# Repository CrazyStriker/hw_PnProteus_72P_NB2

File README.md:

# hw_PnProteus_72P_NB2
PnP adapter board for 72P miata NB2 ECU using Proteus Rusefi compatible board

Onboard debug leds for injectors and ignition as well as vital functions
Clear and simple silk
Fits in the stock ECU case
2x 23 pins ampseal connectors for extended functionalities provided by proteus

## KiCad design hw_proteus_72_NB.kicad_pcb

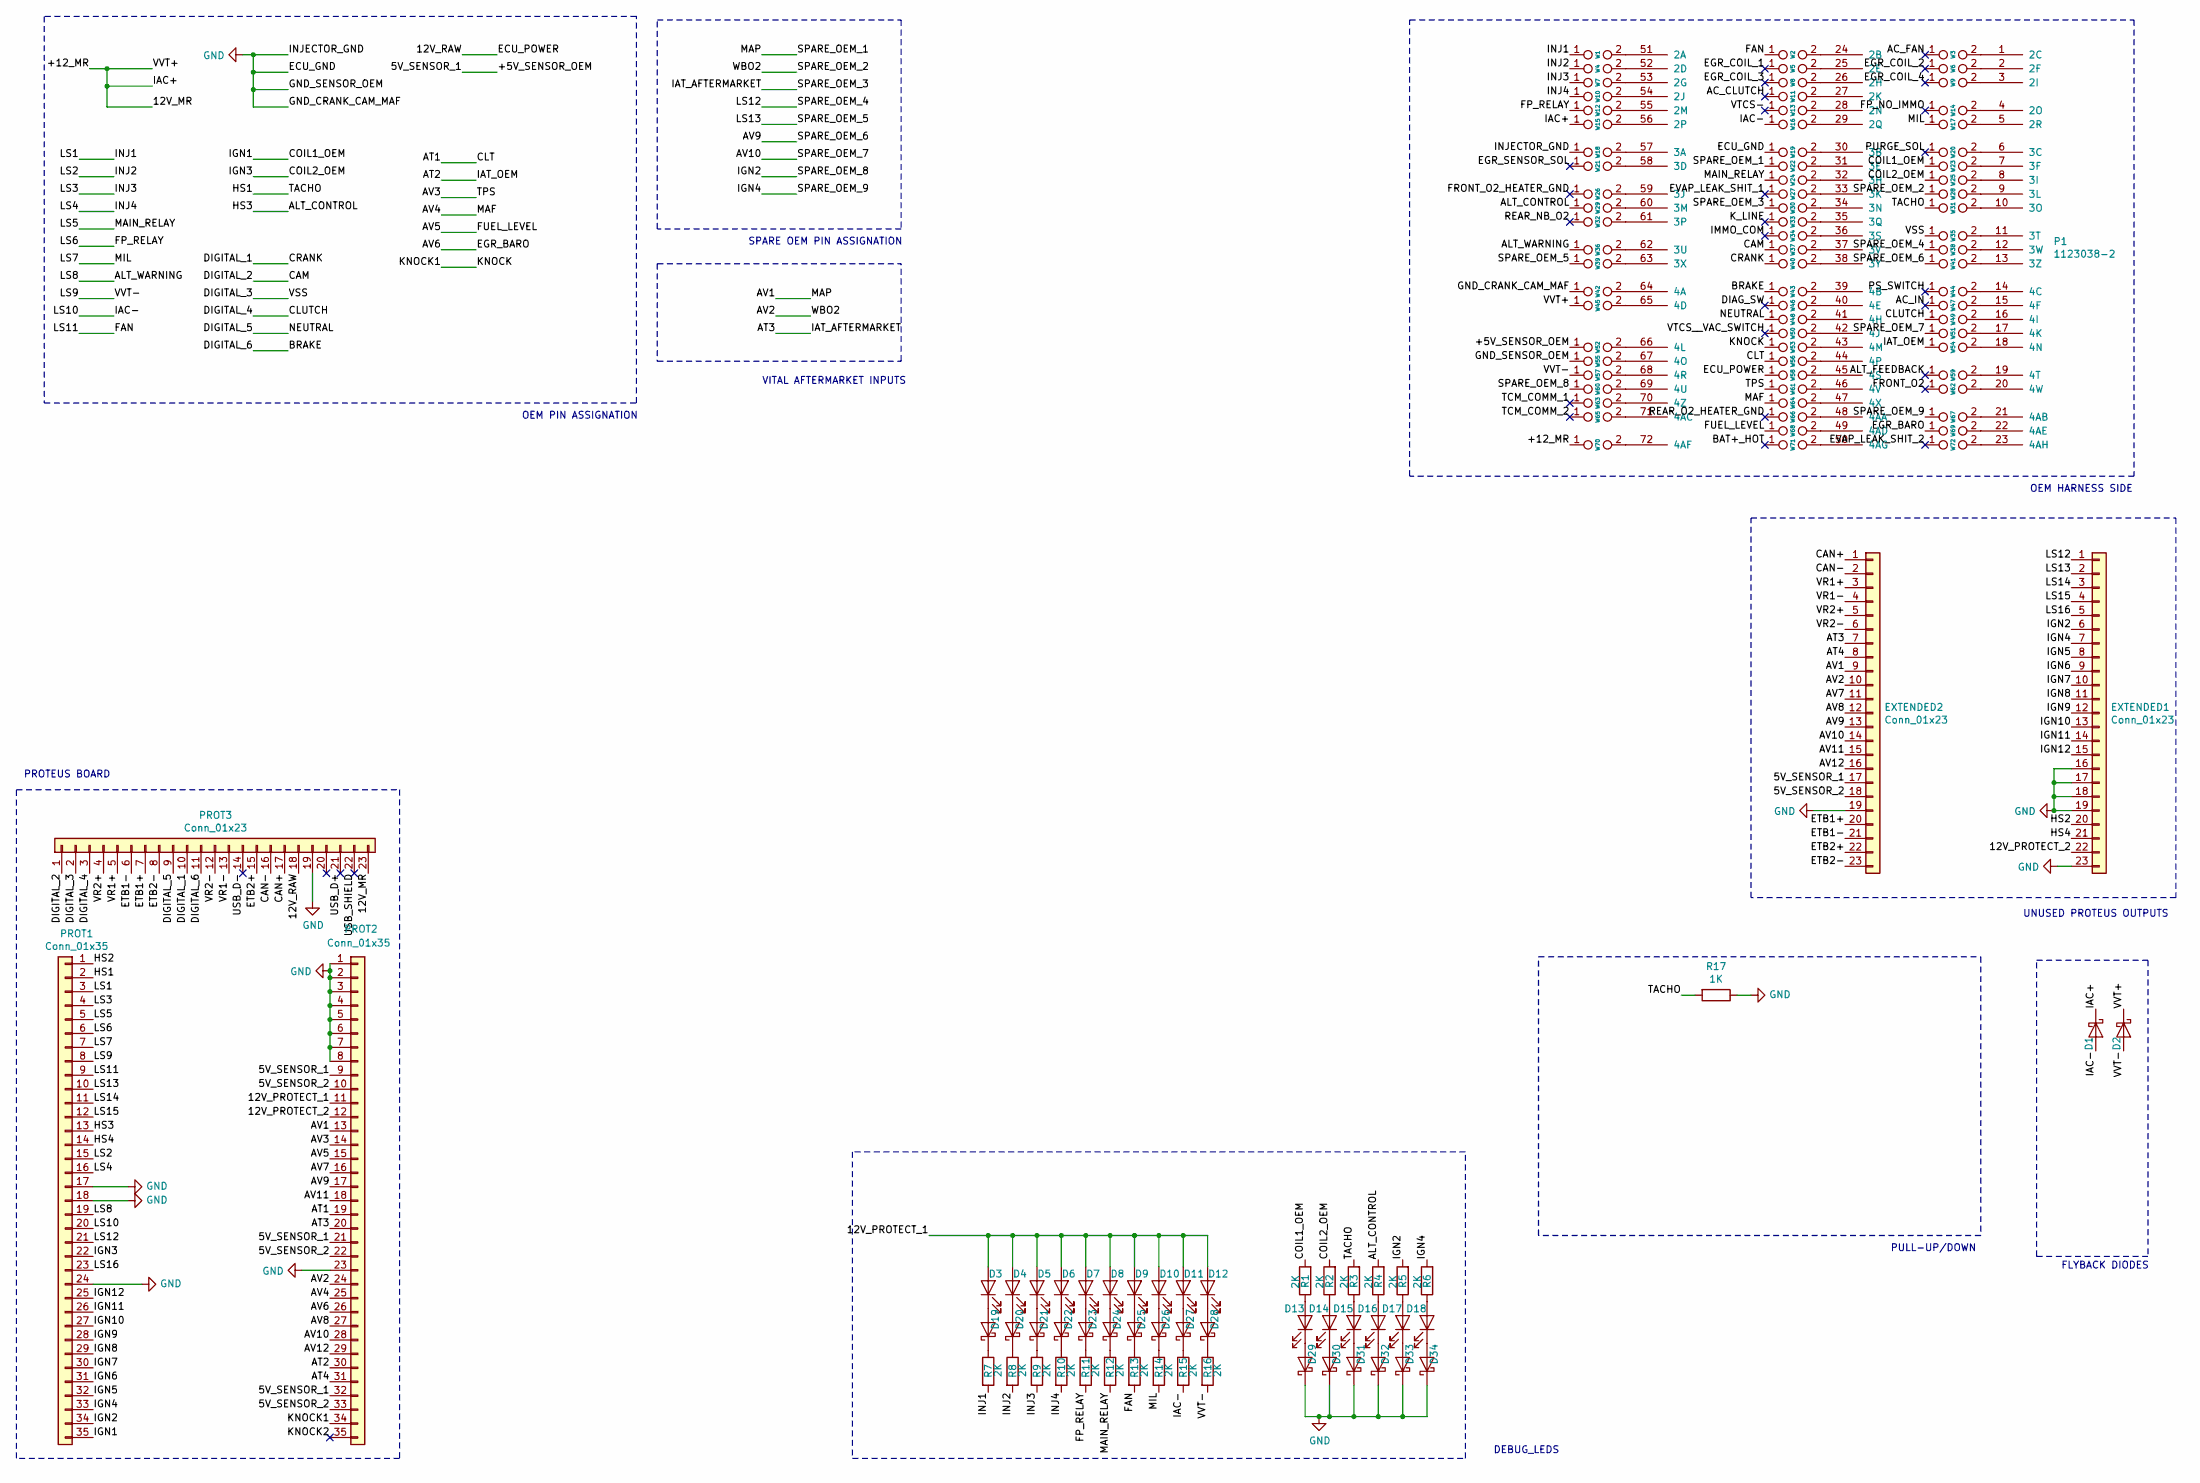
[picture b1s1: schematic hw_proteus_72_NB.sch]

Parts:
D1, D2, D19, D20, D21, D22, D23, D24, D25, D26, D27, D28, D29, D30, D31, D32, D33, D34: D_Schottky; D_SOD-123F
D3, D4, D5, D6, D7, D8, D9, D10, D11, D12, D13, D14, D15, D16, D17, D18: LED; LED_0603_1608Metric_Castellated
EXTENDED1, EXTENDED2: Conn_01x23; ampseal-23
P1: 1123038-2
PROT1, PROT2: Conn_01x35; ampseal-35
PROT3: Conn_01x23; ampseal-23
R1, R2, R3, R4, R5, R6, R7, R8, R9, R10, R11, R12, R13, R14, R15, R16: 2K; R_0603_1608Metric
R17: 1K; R_0201_0603Metric
W1, W2, W3, W4, W5, W6, W7, W8, W9, W10, W11, W12, W13, W14, W15, W16, W17, W18, W19, W20, W21, W22, W23, W24, W25, W26, W27, W28, W29, W30, W31, W32, W33, W34, W35, W36, W37, W38, W39, W40, W41, W42, W43, W44, W45, W46, W47, W48, W49, W50, W51, W52, W53, W54, W55, W56, W57, W58, W59, W60, W61, W62, W63, W64, W65, W66, W67, W68, W69, W70, W71, W72: TestPoint_2Pole; SM0805_jumper

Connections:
/5V_SENSOR_2: EXTENDED2.18, PROT2.10, PROT2.22, PROT2.33
/12V_PROTECT_1: D3.2 (A), D4.2 (A), D5.2 (A), D6.2 (A), D7.2 (A), D8.2 (A), D9.2 (A), D10.2 (A), D11.2 (A), D12.2 (A), PROT2.11
/12V_PROTECT_2: EXTENDED1.22, PROT2.12
/12V_RAW: PROT3.18, W58.1
/+5V_SENSOR_OEM: EXTENDED2.17, PROT2.9, PROT2.21, PROT2.32, W52.1
/+12_MR: D1.1 (K), D2.1 (K), PROT3.23, W15.1, W45.1, W70.1
/AC_CLUTCH: W11.1
/AC_FAN: W3.1
/AC_IN: W47.1
/ALT_CONTROL: PROT1.13, R4.2, W29.1
/ALT_FEEDBACK: W59.1
/ALT_WARNING: PROT1.19, W36.1
/AT1: PROT2.19, W56.1
/AT2: PROT2.30, W54.1
/AT3: EXTENDED2.7, PROT2.20, W30.1
/AT4: EXTENDED2.8, PROT2.31
/AV1: EXTENDED2.9, PROT2.13, W22.1
/AV2: EXTENDED2.10, PROT2.24, W28.1
/AV3: PROT2.14, W61.1
/AV4: PROT2.25, W64.1
/AV5: PROT2.15, W68.1
/AV6: PROT2.26, W69.1
/AV7: EXTENDED2.11, PROT2.16
/AV8: EXTENDED2.12, PROT2.27
/AV9: EXTENDED2.13, PROT2.17, W41.1
/AV10: EXTENDED2.14, PROT2.28, W51.1
/AV11: EXTENDED2.15, PROT2.18
/AV12: EXTENDED2.16, PROT2.29
/BAT+_HOT: W71.1
/BRAKE: PROT3.11, W43.1
/CAM: PROT3.1, W37.1
/CAN+: EXTENDED2.1, PROT3.17
/CAN-: EXTENDED2.2, PROT3.16
/CLUTCH: PROT3.3, W49.1
/COIL1_OEM: PROT1.35, R1.2, W23.1
/COIL2_OEM: PROT1.22, R2.2, W25.1
/CRANK: PROT3.10, W40.1
/DIAG_SW: W46.1
/DIGITAL_3: PROT3.2, W35.1
/DIGITAL_5: PROT3.9, W48.1
/EGR_COIL_1: W5.1
/EGR_COIL_2: W6.1
/EGR_COIL_3: W8.1
/EGR_COIL_4: W9.1
/EGR_SENSOR_SOL: W21.1
/ETB1+: EXTENDED2.20, PROT3.7
/ETB1-: EXTENDED2.21, PROT3.6
/ETB2+: EXTENDED2.22, PROT3.15
/ETB2-: EXTENDED2.23, PROT3.8
/EVAP_LEAK_SHIT_1: W27.1
/EVAP_LEAK_SHIT_2: W72.1
/FAN: PROT1.9, R13.2, W2.1
/FP_NO_IMMO: W14.1
/FP_RELAY: PROT1.6, R11.2, W12.1
/FRONT_O2: W62.1
/FRONT_O2_HEATER_GND: W26.1
/HS1: PROT1.2, R3.2, R17.2, W31.1
/HS2: EXTENDED1.20, PROT1.1
/HS4: EXTENDED1.21, PROT1.14
/IAC-: D1.2 (A), PROT1.20, R15.2, W16.1
/IGN2: EXTENDED1.6, PROT1.34, R5.2, W60.1
/IGN4: EXTENDED1.7, PROT1.33, R6.2, W67.1
/IGN5: EXTENDED1.8, PROT1.32
/IGN6: EXTENDED1.9, PROT1.31
/IGN7: EXTENDED1.10, PROT1.30
/IGN8: EXTENDED1.11, PROT1.29
/IGN9: EXTENDED1.12, PROT1.28
/IGN10: EXTENDED1.13, PROT1.27
/IGN11: EXTENDED1.14, PROT1.26
/IGN12: EXTENDED1.15, PROT1.25
/IMMO_COM: W34.1
/INJ1: PROT1.3, R7.2, W1.1
/INJ2: PROT1.15, R8.2, W4.1
/INJ3: PROT1.4, R9.2, W7.1
/INJ4: PROT1.16, R10.2, W10.1
/KNOCK: PROT2.34, W53.1
/KNOCK2: PROT2.35
/K_LINE: W33.1
/LS5: PROT1.5, R12.2, W24.1
/LS7: PROT1.7, R14.2, W17.1
/LS9: D2.2 (A), PROT1.8, R16.2, W57.1
/LS12: EXTENDED1.1, PROT1.21, W38.1
/LS13: EXTENDED1.2, PROT1.10, W39.1
/LS14: EXTENDED1.3, PROT1.11
/LS15: EXTENDED1.4, PROT1.12
/LS16: EXTENDED1.5, PROT1.23
/PS_SWITCH: W44.1
/PURGE_SOL: W20.1
/REAR_NB_O2: W32.1
/REAR_O2_HEATER_GND: W66.1
/TCM_COMM_1: W63.1
/TCM_COMM_2: W65.1
/USB_D+: PROT3.21
/USB_D-: PROT3.14
/USB_SHIELD: PROT3.22
/VR1+: EXTENDED2.3, PROT3.5
/VR1-: EXTENDED2.4, PROT3.13
/VR2+: EXTENDED2.5, PROT3.4
/VR2-: EXTENDED2.6, PROT3.12
/VTCS-: W13.1
/VTCS__VAC_SWITCH: W50.1
GND: D29.1 (K), D30.1 (K), D31.1 (K), D32.1 (K), D33.1 (K), D34.1 (K), EXTENDED1.16, EXTENDED1.17, EXTENDED1.18, EXTENDED1.19, EXTENDED1.23, EXTENDED2.19, PROT1.17, PROT1.18, PROT1.24, PROT2.1, PROT2.2, PROT2.3, PROT2.4, PROT2.5, PROT2.6, PROT2.7, PROT2.8, PROT2.23, PROT3.19, R17.1, W18.1, W19.1, W42.1, W55.1
unnamed: D10.1 (K), D26.2 (A)
unnamed: D11.1 (K), D27.2 (A)
unnamed: D12.1 (K), D28.2 (A)
unnamed: D13.1 (K), D29.2 (A)
unnamed: D13.2 (A), R1.1
unnamed: D14.1 (K), D30.2 (A)
unnamed: D14.2 (A), R2.1
unnamed: D15.1 (K), D31.2 (A)
unnamed: D15.2 (A), R3.1
unnamed: D16.1 (K), D32.2 (A)
unnamed: D16.2 (A), R4.1
unnamed: D17.1 (K), D33.2 (A)
unnamed: D17.2 (A), R5.1
unnamed: D18.1 (K), D34.2 (A)
unnamed: D18.2 (A), R6.1
unnamed: D19.1 (K), R7.1
unnamed: D3.1 (K), D19.2 (A)
unnamed: D20.1 (K), R8.1
unnamed: D4.1 (K), D20.2 (A)
unnamed: D21.1 (K), R9.1
unnamed: D5.1 (K), D21.2 (A)
unnamed: D22.1 (K), R10.1
unnamed: D6.1 (K), D22.2 (A)
unnamed: D23.1 (K), R11.1
unnamed: D7.1 (K), D23.2 (A)
unnamed: D24.1 (K), R12.1
unnamed: D8.1 (K), D24.2 (A)
unnamed: D25.1 (K), R13.1
unnamed: D9.1 (K), D25.2 (A)
unnamed: D26.1 (K), R14.1
unnamed: D27.1 (K), R15.1
unnamed: D28.1 (K), R16.1
unnamed: P1.1 (2C), W3.2
unnamed: P1.2 (2F), W6.2
unnamed: P1.3 (2I), W9.2
unnamed: P1.4 (2O), W14.2
unnamed: P1.5 (2R), W17.2
unnamed: P1.6 (3C), W20.2
unnamed: P1.7 (3F), W23.2
unnamed: P1.8 (3I), W25.2
unnamed: P1.9 (3L), W28.2
unnamed: P1.10 (3O), W31.2
unnamed: P1.11 (3T), W35.2
unnamed: P1.12 (3W), W38.2
unnamed: P1.13 (3Z), W41.2
unnamed: P1.14 (4C), W44.2
unnamed: P1.15 (4F), W47.2
unnamed: P1.16 (4I), W49.2
unnamed: P1.17 (4K), W51.2
unnamed: P1.18 (4N), W54.2
unnamed: P1.19 (4T), W59.2
unnamed: P1.20 (4W), W62.2
unnamed: P1.21 (4AB), W67.2
unnamed: P1.22 (4AE), W69.2
unnamed: P1.23 (4AH), W72.2
unnamed: P1.24 (2B), W2.2
unnamed: P1.25 (2E), W5.2
unnamed: P1.26 (2H), W8.2
unnamed: P1.27 (2K), W11.2
unnamed: P1.28 (2N), W13.2
unnamed: P1.29 (2Q), W16.2
unnamed: P1.30 (3B), W19.2
unnamed: P1.31 (3E), W22.2
unnamed: P1.32 (3H), W24.2
unnamed: P1.33 (3K), W27.2
unnamed: P1.34 (3N), W30.2
unnamed: P1.35 (3Q), W33.2
unnamed: P1.36 (3S), W34.2
unnamed: P1.37 (3V), W37.2
unnamed: P1.38 (3Y), W40.2
unnamed: P1.39 (4B), W43.2
unnamed: P1.40 (4E), W46.2
unnamed: P1.41 (4H), W48.2
unnamed: P1.42 (4J), W50.2
unnamed: P1.43 (4M), W53.2
unnamed: P1.44 (4P), W56.2
unnamed: P1.45 (4S), W58.2
unnamed: P1.46 (4V), W61.2
unnamed: P1.47 (4X), W64.2
unnamed: P1.48 (4AA), W66.2
unnamed: P1.49 (4AD), W68.2
unnamed: P1.50 (4AG), W71.2
unnamed: P1.51 (2A), W1.2
unnamed: P1.52 (2D), W4.2
unnamed: P1.53 (2G), W7.2
unnamed: P1.54 (2J), W10.2
unnamed: P1.55 (2M), W12.2
unnamed: P1.56 (2P), W15.2
unnamed: P1.57 (3A), W18.2
unnamed: P1.58 (3D), W21.2
unnamed: P1.59 (3J), W26.2
unnamed: P1.60 (3M), W29.2
unnamed: P1.61 (3P), W32.2
unnamed: P1.62 (3U), W36.2
unnamed: P1.63 (3X), W39.2
unnamed: P1.64 (4A), W42.2
unnamed: P1.65 (4D), W45.2
unnamed: P1.66 (4L), W52.2
unnamed: P1.67 (4O), W55.2
unnamed: P1.68 (4R), W57.2
unnamed: P1.69 (4U), W60.2
unnamed: P1.70 (4Z), W63.2
unnamed: P1.71 (4AC), W65.2
unnamed: P1.72 (4AF), W70.2

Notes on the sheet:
PROTEUS BOARD
OEM HARNESS SIDE
UNUSED PROTEUS OUTPUTS
OEM PIN ASSIGNATION
DEBUG_LEDS
SPARE OEM PIN ASSIGNATION
VITAL AFTERMARKET INPUTS
FLYBACK DIODES
PULL-UP/DOWN

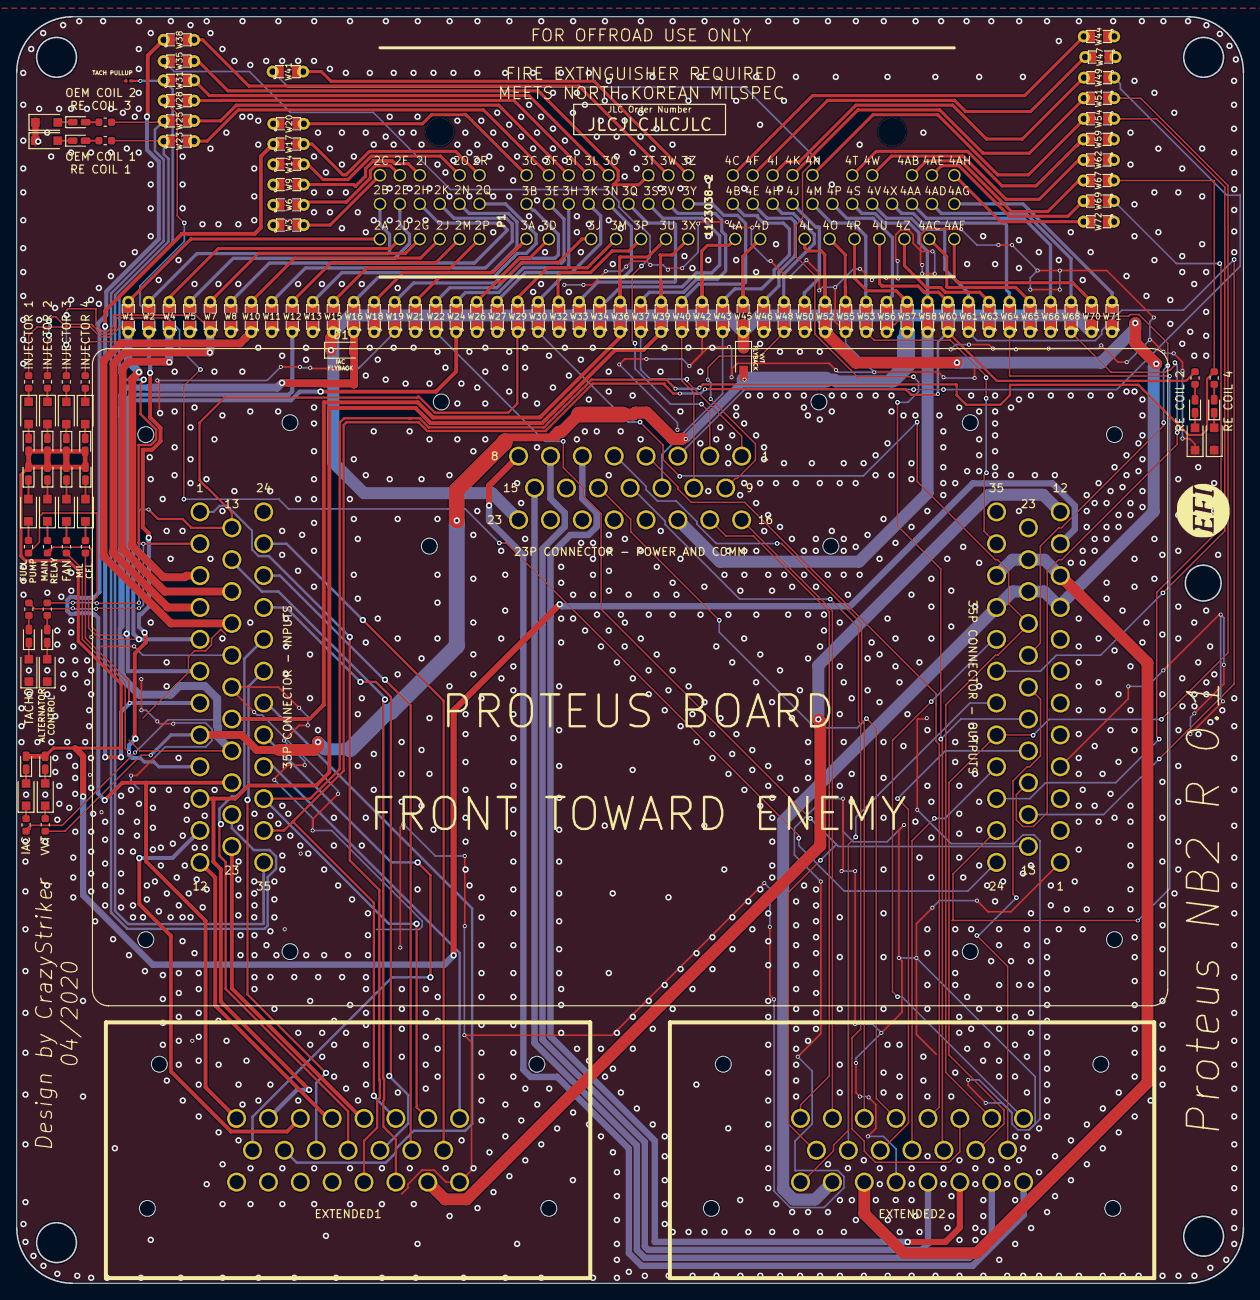
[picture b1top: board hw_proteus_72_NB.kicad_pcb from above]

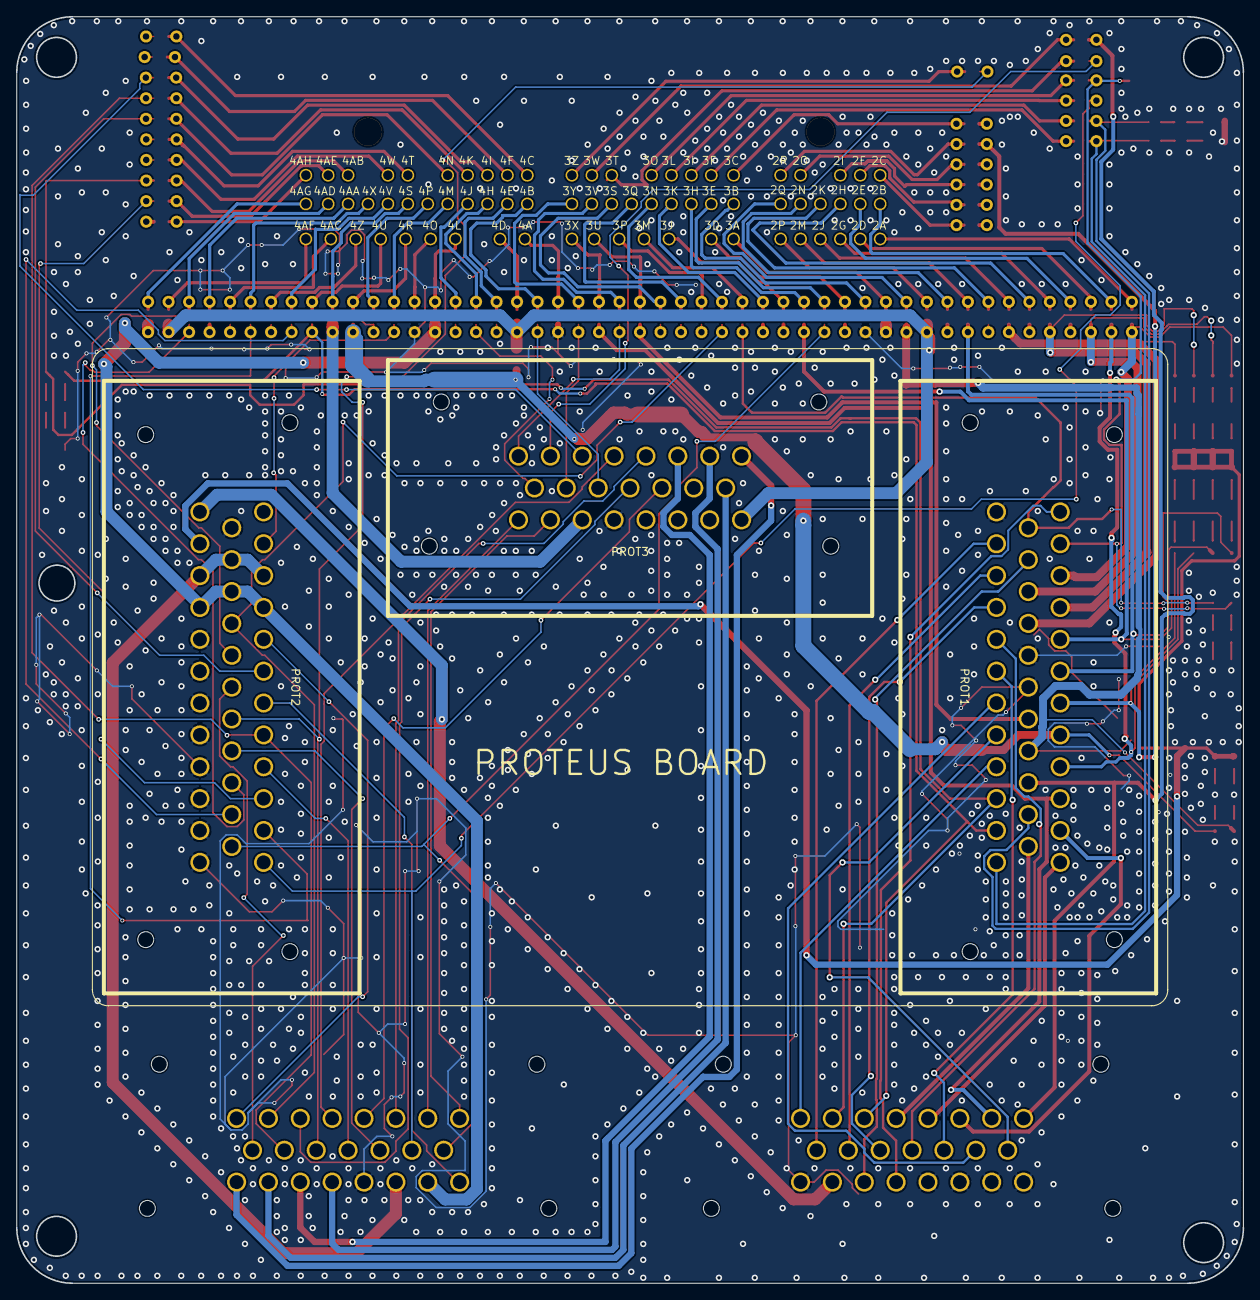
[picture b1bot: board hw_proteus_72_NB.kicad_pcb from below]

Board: 2 copper layers, 154.0 x 159.0 mm, 131 parts (3 on the bottom side), 176 nets.

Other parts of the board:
LOGO1: LOGO
LOGO2: LOGO; JLC_PCB_TAG

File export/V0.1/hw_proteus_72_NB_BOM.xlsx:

Comment | Designator | Footprint | LCSC Part #
2K | R17,R16,R15,R14,R13,R12,R11,R10,R9,R8,R7,R6,R5,R4,R3,R2,R1 | R_0603_1608Metric | C4190
Conn_01x23 | EXTENDED2,EXTENDED1,PROT3 | ampseal-23
D_Schottky | D34,D33,D32,D31,D30,D29,D28,D27,D26,D25,D24,D23,D22,D21,D20,D19,D2,D1 | D_SOD-123F | C64898
LED | D18,D17,D16,D15,D14,D13,D12,D11,D10,D9,D8,D7,D6,D5,D4,D3 | LED_0603_1608Metric_Castellated | C2286
TestPoint_2Pole | W72,W71,W70,W69,W68,W67,W66,W65,W64,W63,W62,W61,W60,W59,W58,W57,W56,W55,W54,W53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 | SM0805_jumper | C17477
Conn_01x35 | PROT2,PROT1 | ampseal-35
1123038-2 | P1 | 1123038-2
LOGO | LOGO1 | LOGO
LOGO | LOGO2 | JLC_PCB_TAG

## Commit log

2020-04-12 start
2020-04-12 repo refactoring
2020-04-13 Added knock sensing connection
2020-04-16 Beefed up injector wires, as well as VVT and IAC low sides. Started the ground stitching process, TBC
2020-04-17 switched LS and HS outputs to match hardware timers distribution. Added a 2k pulldown for the tach output"
